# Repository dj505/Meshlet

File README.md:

# [Meshlet V2](https://5panel.dance/Meshlet)

Meshlet is an open-source and feature-packed LoRa mesh network node, designed to be compatible (but not affiliated) with the Meshtastic® project. It's made to be deployed just about anywhere you want it to be - you can plug in a solar panel and set it up outside, turn it into a pocketable every-day-carry node, wire it up to your car as a mobile repeater, or even just leave it on a windowsill attached to a BBS script/Meshsense/etc. 

**Table of Contents**
1. [Features](#features)
2. [Project Sponsor](#project-sponsor)
3. [Real World Testing](#real-world-testing)
5. [Meshlet Docs](#meshlet-docs)

## Features
Features include, but are not limited to...
- USB C, with configurable charge rate limit (250mA, 500mA, 1A)
- LiPo/LiIon and LiFePo4 support
- ESD/TVS protection on the USB port
- Solar input (as well as constant DC input) from 3.3V to 18V, tolerant up to 25V
  - Flexible wiring methods, with dedicated JST PH footprints as well as pads to directly solder wires to!
  - Tested & working with as little as a cheap 80mm 5v solar panel, on an overcast Canadian winter day!
  - Unlike many boards that need a manual reset after too little sunlight drains the battery, the Meshlet should recover on its own!
- Smart power path management, thanks to the BQ25185. No need to worry about unnecessarily cycling the battery!
- JST 2.0 and Picoblade 1.5mm battery connector footprints, to hopefully fit whatever LiPos you've got laying around
- Low operating power, measuring as low as 2.8mA idle current draw (without WiFi)
- Active current/voltage monitoring and reporting on 3 channels over the mesh, via INA3221
  - Ch. 1: Battery
  - Ch. 2: USB & external power
  - Ch. 3: BQ25185 regulated battery output
- Up to 8MB onboard flash
- WIO-SX1262 LoRa radio
- BME280 temperature/humidity/barometric pressure sensor
- I2C expansion port
- Dedicated 3.3V regulators for all major components, each with its own self-resetting fuse, to ensure stable power
- "External notification" header for a MOSFET-driven 3.3V buzzer, LED, vibration motor, etc
- Raspberry Pi RM2 for optional WiFi (and Bluetooth, whenever the firmware supports it)
- Total footprint size of ~42*32mm, less than half the size of a credit card!

## Project Sponsor
This project is sponsored by [PCBWay](https://pcbway.com)! Absolutely massive thank you to them for helping make these projects possible for me.

If you're interested in DIY electronics, I'm sure you're familiar with the name. PCBWay is a manufacturing company specializing in circuit boards, but they also offer services for SMT assembly, CNC milling, 3D printing, sheet metal fabrication, and injection molding! They can manufacture all of the parts for your hobby project, in one convenient place, with fine-grained control over the entire manufacturing process.

I relied pretty heavily on their PCB manufacturing and SMT assembly services to get the final revision of the Meshlet project built & tested. In my past experience, their boards always come out beautiful and pretty near perfect, and these ones are no exception. Their engineers were in contact with me from start to finish, making sure that everything was correct and to spec throughout each step of the process. They sourced all of the parts based on the BOM I provided, ensured that each pick lined up with what I needed, and even sent confirmation photos before the assembly process to ensure that every part was placed & oriented properly. When I mistakenly selected two parts to fit a single footprint, they agreed with my request to ship me the extra parts that I had them order alongside the PCBs, for me to solder by hand if needed after I receive them!

Sponsors like this make a huge difference in allowing me to continue testing & iterating on projects like this one. Without this opportunity, it likely would have stopped at the first revision prototype! Thanks again to PCBWay for reaching out and organizing this opportunity. Please [check them out](https://pcbway.com), and definitely consider using their services for your next project! 

## Real World Testing
Meshlet has been tested in a variety of real-world use cases thus far, including...
- **Building side solar repeater:** An early Meshlet V2 revision (1.0) installed inside a weatherproof box, with a 5V solar panel and 3000mAh LiPo, in late winter conditions. Runs Meshtastic in CLIENT_BASE mode. Uptime as of writing is roughly a month, with zero resets or brownouts. Battery life has not dropped below 40%. Average draw is 28-32mA, plus an extra 8-12mA due to a secondary nRF52 MeshCore repeater node being powered via the 3v3 peripheral pins.
- **Cheap garden light repeater:** A latest revision Meshlet V2 (1.1) installed inside a cheap solar garden light from Home Depot. Solar panel has been wired directly to the solar input. Powered by two 1000mAh parallel LiFePO4 18500 batteries that came with the light. Has not yet dropped below 50% in 1 week of testing. Runs MeshCore, as a repeater.
- **Handheld unit:** An early revision Meshlet V2 (1.0) in a custom 3D printed case, with an I2C OLED and M5Stack CardKB soldered to the I2C breakout. Powered by a 3000mAh battery. Running Meshtastic. Has not yet undergone extensive testing, but showed promise with a battery life lasting at least 3 days with the CLIENT_MUTE role.
- **Bench testing:** Early revision Meshlet V2 (1.0) in the plastic case from a Heltec T114, powered by a recycled 1000mAh vape battery. Has undergone testing with several different solar panels (4V-7V), DC power supplies (5V-12V), charge rates, and I2C peripherals. Has been able to handle everything I've thrown at it so far. Survived having both a solar panel and a battery being plugged in with the incorrect polarity on separate occasions.

## Meshlet Docs
Assembly notes, firmware, and usage notes can all be found on [the Meshlet webpage.](https://www.5panel.dance/Meshlet/)

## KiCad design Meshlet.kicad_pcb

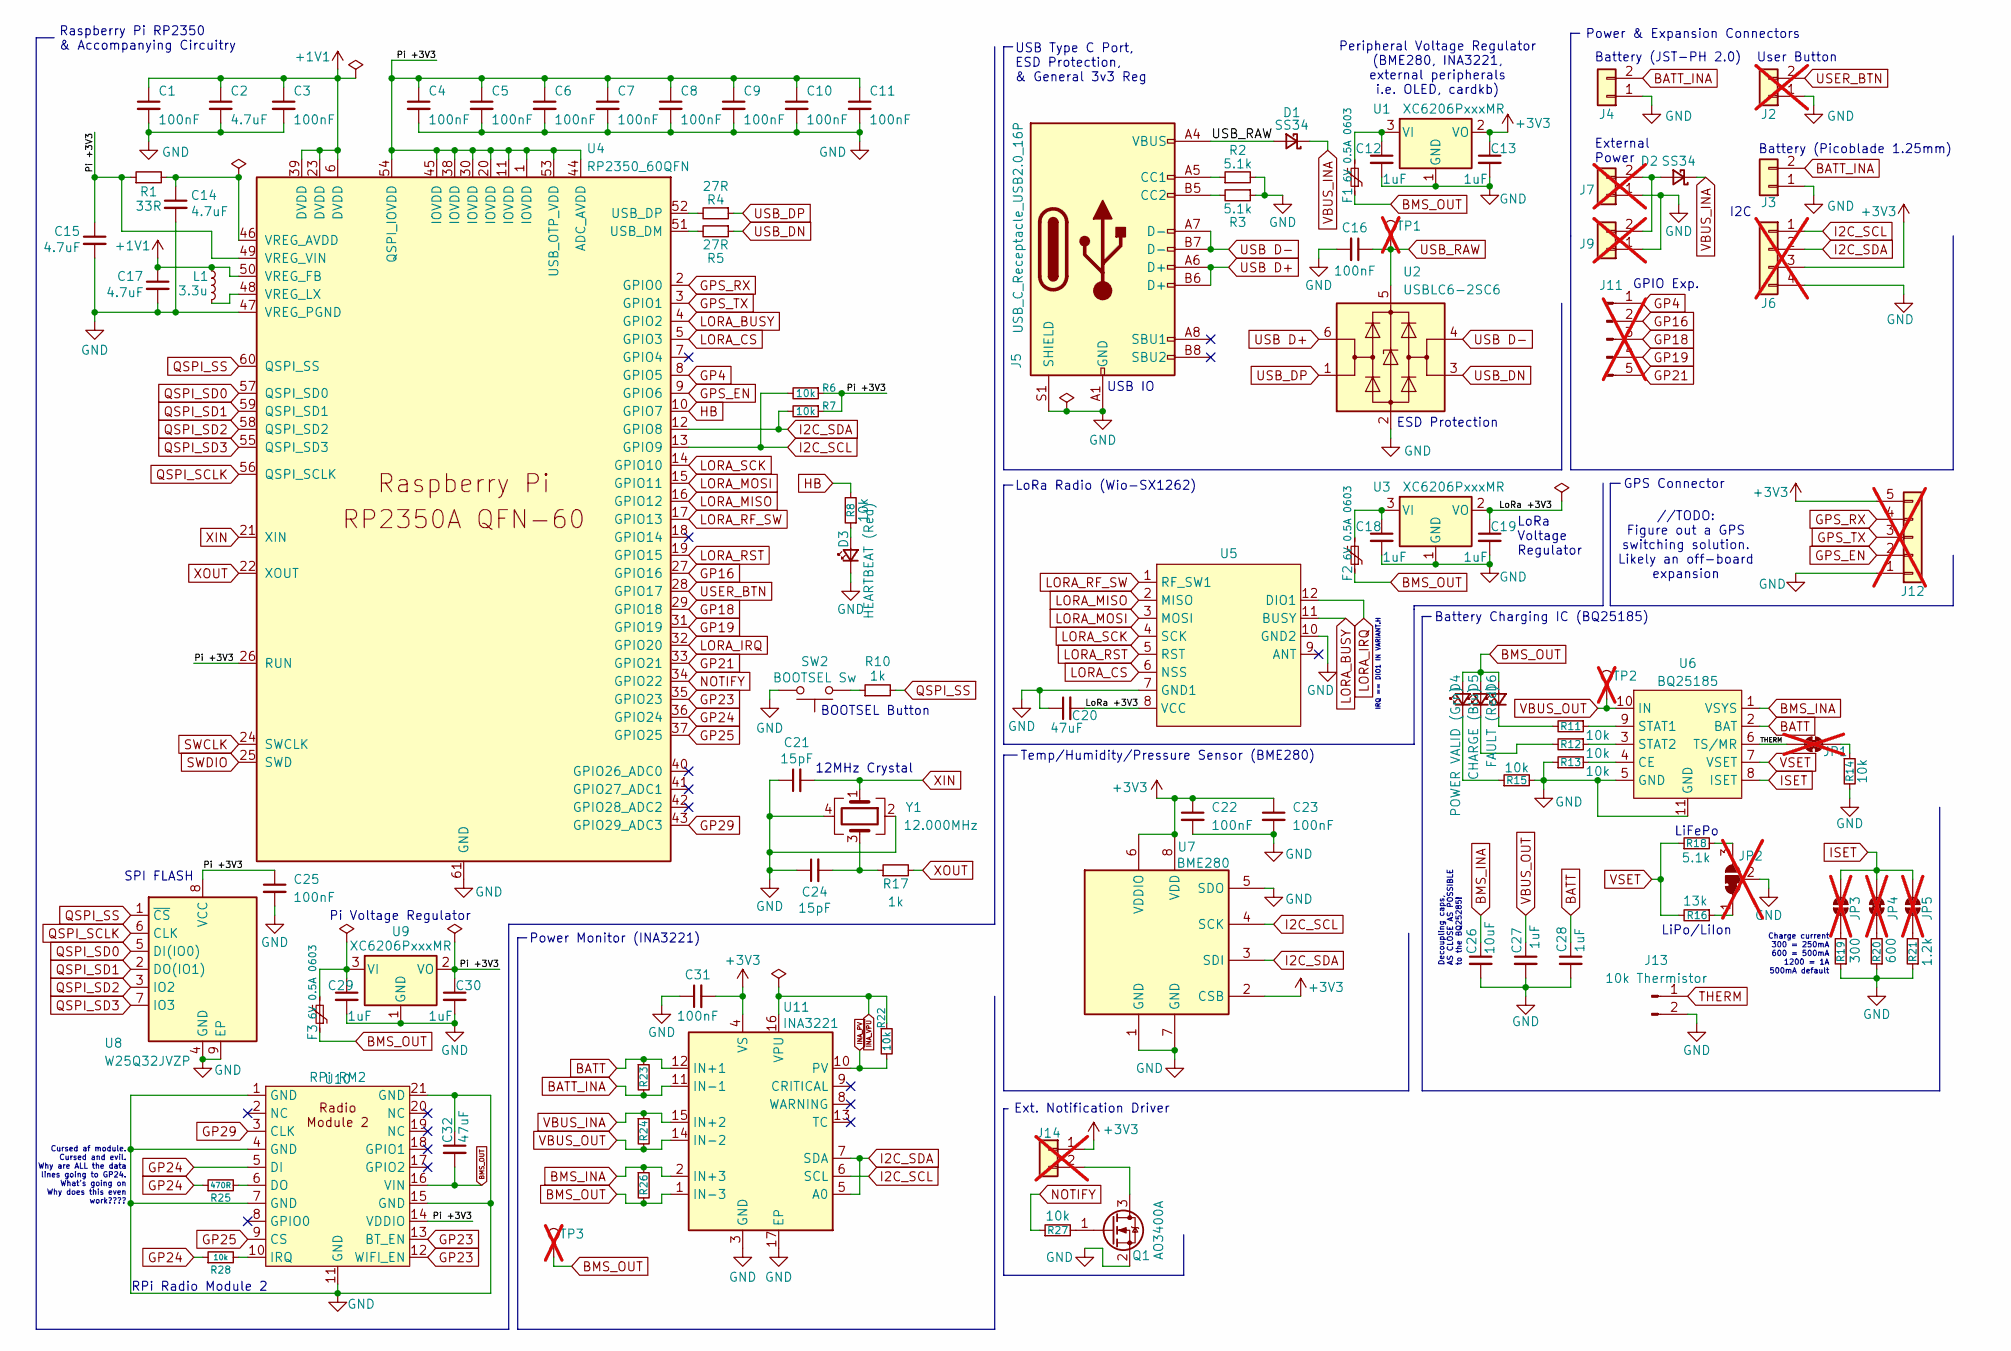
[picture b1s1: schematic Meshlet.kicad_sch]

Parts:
C1, C3, C4, C5, C6, C7, C8, C9, C10, C11, C16, C22, C23, C25, C31: 100nF; C_0402_1005Metric; LCSC C1525
C2, C14: 4.7uF; C_0402_1005Metric; LCSC C23733
C12, C13, C18, C19, C29, C30: 1uF; C_0402_1005Metric; LCSC C52923
C15, C17: 4.7uF; C_0402_1005Metric_small_pads; LCSC C23733
C20, C32: 47uF; C_0805_2012Metric; LCSC C16780
C21, C24: 15pF; C_0402_1005Metric; LCSC C1548
C26: 10uF; C_0402_1005Metric; LCSC C105226
C27, C28: 1uF; C_0402_1005Metric; LCSC C105226
D1, D2: SS34; D_SMA; LCSC C8678
D3: HEARTBEAT (Red); LED_0603_1608Metric; LCSC C2290
D4: POWER VALID (Grn); LED_0603_1608Metric; LCSC C2290
D5: CHARGE (Blu); LED_0603_1608Metric; LCSC C2290
D6: FAULT (Red); LED_0603_1608Metric; LCSC C2286
F1, F2, F3: 6V 0.5A 0603; Fuse_0603_1608Metric; LCSC C69679
J2: User Btn Header; PinHeader_1x02_P2.00mm_Vertical; not fitted
J3: Batt. Header (Picoblade 1.25); Molex_PicoBlade_53261-0271_1x02-1MP_P1.25mm_Horizontal; LCSC C177225
J4: Batt. Header (JST-PH 2.0); JST_PH_S2B-PH-SM4-TB_1x02-1MP_P2.00mm_Horizontal; LCSC C47647
J5: USB_C_Receptacle_USB2.0_16P; USB_C_Receptacle_G-Switch_GT-USB-7010ASV; LCSC C393939
J6: I2C Header; PinHeader_1x04_P2.00mm_Vertical; not fitted
J7: Ext. Power Header; JST_PH_S2B-PH-SM4-TB_1x02-1MP_P2.00mm_Horizontal; LCSC C27910; not fitted
J9: Ext. Power Header; PinHeader_1x02_P2.54mm_Vertical; not fitted
J11: GPIO Exp.; PinHeader_1x05_P2.00mm_Vertical; not fitted
J12: GPS Header; PinHeader_1x05_P1.27mm_Vertical; not fitted
J13: 10k Thermistor; PinHeader_1x02_P2.54mm_Vertical
J14: Ext. Notif. Header; PinHeader_1x02_P2.00mm_Vertical; not fitted
JP1: TS; SolderJumper-2_P1.3mm_Bridged_RoundedPad1.0x1.5mm; not fitted
JP2: Chemistry Select; SolderJumper-3_P1.3mm_Bridged12_RoundedPad1.0x1.5mm; not fitted
JP3: 250mA Charge; SolderJumper-2_P1.3mm_Open_RoundedPad1.0x1.5mm; not fitted
JP4: 500mA Charge; SolderJumper-2_P1.3mm_Bridged_RoundedPad1.0x1.5mm; not fitted
JP5: 1A Charge; SolderJumper-2_P1.3mm_Open_RoundedPad1.0x1.5mm; not fitted
L1: 3.3u; L_pol_2016; LCSC C42411119
Q1: AO3400A; SOT-23; LCSC C20917
R1: 33R; R_0402_1005Metric; LCSC C25105
R2, R3, R18: 5.1k; R_0402_1005Metric; LCSC C25905
R4, R5: 27R; R_0402_1005Metric; LCSC C25100
R6, R7, R8, R11, R12, R13, R14, R15, R22, R27, R28: 10k; R_0402_1005Metric; LCSC C25744
R10, R17: 1k; R_0402_1005Metric; LCSC C11702
R16: 13k; R_0402_1005Metric; LCSC C25754
R19: 300; R_0402_1005Metric; LCSC C25102
R20: 600; R_0402_1005Metric; LCSC C25126
R21: 1.2k; R_0402_1005Metric; LCSC C25862
R23, R24, R26: PA2512FKF7W0R01E; R_2512_6332Metric; LCSC C875838
R25: 470R; R_0402_1005Metric; LCSC C25117
SW2: BOOTSEL Sw; SW_Push_1P1T_XKB_TS-1187A; LCSC C318884
TP1, TP2, TP3: TestPoint; TestPoint_Pad_D1.0mm; not fitted
U1, U3, U9: XC6206PxxxMR; SOT-23-3; LCSC C5446
U2: USBLC6-2SC6; SOT-23-6; LCSC C2687116
U4: RP2350_60QFN; RP2350-QFN-60-1EP_7x7_P0.4mm_EP3.4x3.4mm_ThermalVias; LCSC C42411118
U5: Wio-SX1262
U6: BQ25185; Texas_DLH0010A_WSON-10-1EP_2.2x2mm_P0.4mm_EP0.9x1.5mm_Therm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; LCSC C19725033
U7: BME280; Bosch_LGA-8_2.5x2.5mm_P0.65mm_ClockwisePinNumbering; LCSC C92489
U8: W25Q32JVZP; WSON-8-1EP_6x5mm_P1.27mm_EP3.4x4.3mm; LCSC C2940197
U10: RPi RM2; Radio Module 2
U11: INA3221; Texas_RGV0016A_VQFN-16-1EP_4x4mm_P0.65mm_EP2.1x2.1mm; LCSC C181255
Y1: 12.000MHz; Crystal_SMD_3225-4Pin_3.2x2.5mm; LCSC C20625731

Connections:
+1V1: C1.1, C2.1, C3.1, C17.1, L1.1, U4.6 (DVDD), U4.23 (DVDD), U4.39 (DVDD), U4.50 (VREG_FB)
+3V3: C13.1, C22.1, C23.1, C31.2, J6.3, J12.5, J14.1, U1.2 (VO), U7.2 (CSB), U7.6 (VDDIO), U7.8 (VDD), U11.4 (VS)
/LoRa +3V3: C19.1, C20.2, U3.2 (VO), U5.8 (VCC)
/Pi +3V3: C4.1, C5.1, C6.1, C7.1, C8.1, C9.1, C10.1, C11.1, C15.1, C25.1, C30.1, R1.1, R6.1, R7.1, U4.1 (IOVDD), U4.11 (IOVDD), U4.20 (IOVDD), U4.26 (RUN), U4.30 (IOVDD), U4.38 (IOVDD), U4.44 (ADC_AVDD), U4.45 (IOVDD), U4.49 (VREG_VIN), U4.53 (USB_OTP_VDD), U4.54 (QSPI_IOVDD), U8.8 (VCC), U9.2 (VO), U10.14 (VDDIO)
BATT: C28.1, R23.1, U6.2 (BAT), U11.12 (IN+1)
BATT_INA: J3.2, J4.2, R23.2, U11.11 (IN-1)
BMS_INA: C26.1, R26.1, U6.1 (VSYS), U11.2 (IN+3)
BMS_OUT: C32.2, D4.2 (A), D5.2 (A), D6.2 (A), F1.1, F2.1, F3.1, R26.2, TP3.1, U10.16 (VIN), U11.1 (IN-3)
GND: C1.2, C2.2, C3.2, C4.2, C5.2, C6.2, C7.2, C8.2, C9.2, C10.2, C11.2, C12.2, C13.2, C14.2, C15.2, C16.2, C17.2, C18.2, C19.2, C20.1, C21.1, C22.2, C23.2, C24.1, C25.2, C26.2, C27.2, C28.2, C29.2, C30.2, C31.1, C32.1, D3.1 (K), J2.1, J3.1, J4.1, J5.A1 (GND), J5.A12 (GND), J5.B1 (GND), J5.B12 (GND), J5.S1 (SHIELD), J6.4, J7.1, J9.1, J12.1, J13.2, JP2.2 (C), Q1.2 (S), R2.2, R3.1, R13.1, R14.2, R15.2, R19.1, R20.1, R21.1, SW2.2, U1.1 (GND), U2.2 (GND), U3.1 (GND), U4.47 (VREG_PGND), U4.61 (GND), U5.7 (GND1), U5.10 (GND2), U6.5 (GND), U6.11 (GND), U7.1 (GND), U7.5 (SDO), U7.7 (GND), U8.4 (GND), U8.9 (EP), U9.1 (GND), U10.1 (GND), U10.4 (GND), U10.7 (GND), U10.11 (GND), U10.15 (GND), U10.21 (GND), U11.3 (GND), U11.17 (EP), Y1.2, Y1.4
GP4: J11.1, U4.8 (GPIO5)
GP16: J11.2, U4.27 (GPIO16)
GP18: J11.3, U4.29 (GPIO18)
GP19: J11.4, U4.31 (GPIO19)
GP21: J11.5, U4.33 (GPIO21)
GP23: U4.35 (GPIO23), U10.12 (WIFI_EN), U10.13 (BT_EN)
GP24: R25.1, R28.1, U4.36 (GPIO24), U10.5 (DI)
GP25: U4.37 (GPIO25), U10.9 (CS)
GP29: U4.43 (GPIO29_ADC3), U10.3 (CLK)
GPS_EN: J12.2, U4.9 (GPIO6)
GPS_RX: J12.4, U4.2 (GPIO0)
GPS_TX: J12.3, U4.3 (GPIO1)
HB: R8.2, U4.10 (GPIO7)
I2C_SCL: J6.1, R6.2, U4.13 (GPIO9), U7.4 (SCK), U11.6 (SCL)
I2C_SDA: J6.2, R7.2, U4.12 (GPIO8), U7.3 (SDI), U11.5 (A0), U11.7 (SDA)
INA_PV: R22.2, U11.10 (PV)
INA_VPU: R22.1, U11.16 (VPU)
ISET: JP3.2 (B), JP4.2 (B), JP5.2 (B), U6.8 (ISET)
LORA_BUSY: U4.4 (GPIO2), U5.11 (BUSY)
LORA_CS: U4.5 (GPIO3), U5.6 (NSS)
LORA_IRQ: U4.32 (GPIO20), U5.12 (DIO1)
LORA_MISO: U4.16 (GPIO12), U5.2 (MISO)
LORA_MOSI: U4.15 (GPIO11), U5.3 (MOSI)
LORA_RF_SW: U4.17 (GPIO13), U5.1 (RF_SW1)
LORA_RST: U4.19 (GPIO15), U5.5 (RST)
LORA_SCK: U4.14 (GPIO10), U5.4 (SCK)
NOTIFY: R27.1, U4.34 (GPIO22)
unnamed: C24.2, R17.1, Y1.3
unnamed: D2.2 (A), J7.2, J9.2
unnamed: D3.2 (A), R8.1
unnamed: D4.1 (K), R15.1
unnamed: D5.1 (K), R12.2
unnamed: D6.1 (K), R11.2
unnamed: J5.A5 (CC1), R2.1
unnamed: J5.B5 (CC2), R3.2
unnamed: J14.2, Q1.3 (D)
unnamed: JP1.2 (B), R14.1
unnamed: JP2.1 (A), R16.1
unnamed: JP2.3 (B), R18.2
unnamed: JP3.1 (A), R19.2
unnamed: JP4.1 (A), R20.2
unnamed: JP5.1 (A), R21.2
unnamed: Q1.1 (G), R27.2
unnamed: R10.1, SW2.1
unnamed: C12.1, F1.2, U1.3 (VI)
unnamed: C18.1, F2.2, U3.3 (VI)
unnamed: R5.2, U4.51 (USB_DM)
unnamed: R4.2, U4.52 (USB_DP)
unnamed: C14.1, R1.2, U4.46 (VREG_AVDD)
unnamed: L1.2, U4.48 (VREG_LX)
unnamed: R13.2, U6.4 (CE)
unnamed: R11.1, U6.9 (STAT1)
unnamed: R12.1, U6.3 (STAT2)
unnamed: C29.1, F3.2, U9.3 (VI)
unnamed: R25.2, U10.6 (DO)
unnamed: R28.2, U10.10 (IRQ)
QSPI_SCLK: U4.56 (QSPI_SCLK), U8.6 (CLK)
QSPI_SD0: U4.57 (QSPI_SD0), U8.5 (DI(IO0))
QSPI_SD1: U4.59 (QSPI_SD1), U8.2 (DO(IO1))
QSPI_SD2: U4.58 (QSPI_SD2), U8.3 (IO2)
QSPI_SD3: U4.55 (QSPI_SD3), U8.7 (IO3)
QSPI_SS: R10.2, U4.60 (QSPI_SS), U8.1 (~CS)
SWCLK: U4.24 (SWCLK)
SWDIO: U4.25 (SWD)
THERM: J13.1, JP1.1 (A), U6.6 (TS/MR)
USB D+: J5.A6 (D+), J5.B6 (D+), U2.6 (I/O1)
USB D-: J5.A7 (D-), J5.B7 (D-), U2.4 (I/O2)
USB_DN: R5.1, U2.3 (I/O2)
USB_DP: R4.1, U2.1 (I/O1)
USB_RAW: C16.1, D1.2 (A), J5.A4 (VBUS), J5.A9 (VBUS), J5.B4 (VBUS), J5.B9 (VBUS), TP1.1, U2.5 (VBUS)
USER_BTN: J2.2, U4.28 (GPIO17)
VBUS_INA: D1.1 (K), D2.1 (K), R24.1, U11.15 (IN+2)
VBUS_OUT: C27.1, R24.2, TP2.1, U6.10 (IN), U11.14 (IN-2)
VSET: R16.2, R18.1, U6.7 (VSET)
XIN: C21.2, U4.21 (XIN), Y1.1
XOUT: R17.2, U4.22 (XOUT)

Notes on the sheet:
Charge current 300 = 250mA 600 = 500mA 1200 = 1A 500mA default
I2C
LoRa Voltage Regulator
IRQ == DIO1 IN VARIANT.H
12MHz Crystal
LiFePo
Pi Voltage Regulator
SPI FLASH
Power Monitor (INA3221)
Cursed af module. Cursed and evil. Why are ALL the data lines going to GP24. What's going on Why does this even work????
Battery Charging IC (BQ25185)
Battery (JST-PH 2.0)
External Power
LoRa Radio (Wio-SX1262)
User Button
ESD Protection
Power & Expansion Connectors
Ext. Notification Driver
USB Type C Port, ESD Protection, & General 3v3 Reg
Raspberry Pi RP2350 & Accompanying Circuitry
Peripheral Voltage Regulator (BME280, INA3221, external peripherals i.e. OLED, cardkb)
//TODO: Figure out a GPS switching solution. Likely an off-board expansion
Temp/Humidity/Pressure Sensor (BME280)
GPIO Exp.
USB IO
Decoupling caps, AS CLOSE AS POSSIBLE to the BQ25285!
RPi Radio Module 2
LiPo/LiIon
Battery (Picoblade 1.25mm)
GPS Connector
BOOTSEL Button

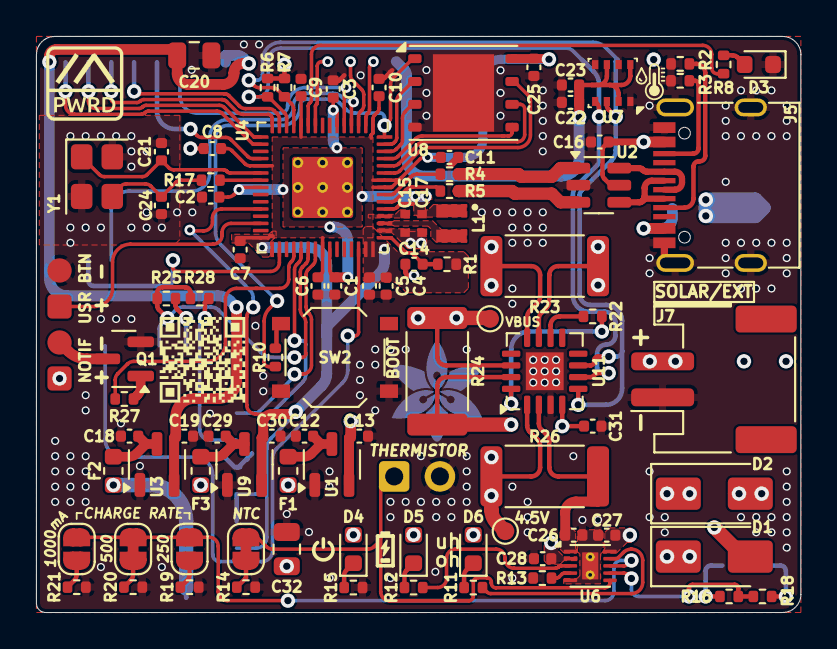
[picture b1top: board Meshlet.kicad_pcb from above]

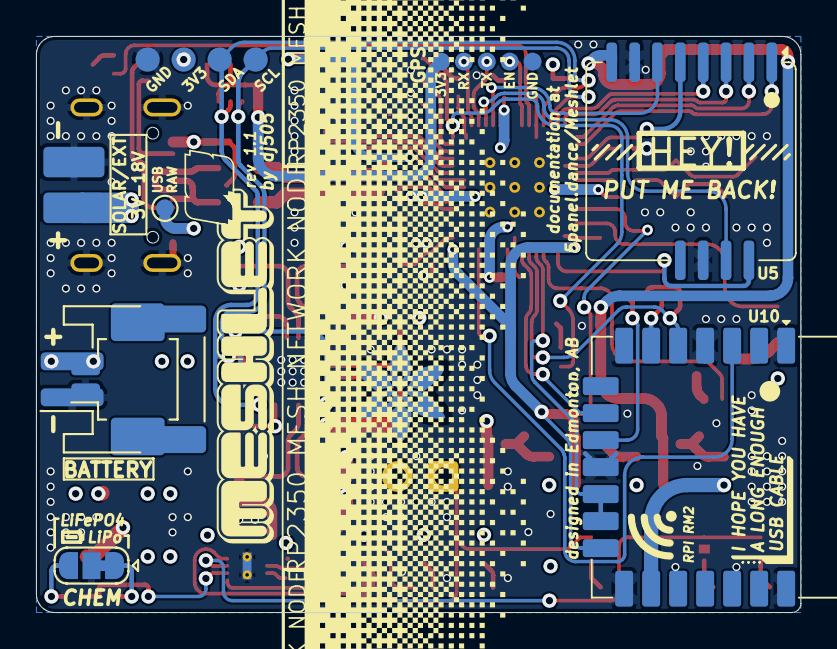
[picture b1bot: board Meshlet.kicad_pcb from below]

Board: 4 copper layers, 42.5 x 32.0 mm, 101 parts (9 on the bottom side), 78 nets.

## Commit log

2025-07-21 Initial commit - finished schematic
2025-07-27 PCB routing like 99% done oops
2025-08-03 Custom Pi RM2 symbol/footprint, silkscreen gfx
2025-08-03 Tooling holes, silkscreen changes
2025-08-03 fix picoblade battery polarity hopefully 🤞
2025-08-03 Fixed exposed ground between jumper pads, yikes
2025-08-04 appease the trademark gods
2025-08-05 docs
2025-08-05 haha oops
2025-08-06 Fixed stemma port pin order, more touchups
2025-08-06 Ground fill thermal spoke bug workaround for RM2
2025-08-07 Better thermal relief bug workaround?
2025-08-14 Silkscreen changes, added BQ24074 output breakout
2025-12-29 Fixed several design flaws. More caps, more LDOs, etc
2026-01-03 Major changes to schematic
    Replace BQ24074 with BQ25185, remove extraneous passives, simplified several areas, add extra GPIO breakouts, reannotated schematic, etc.
2026-01-07 Redesign!
2026-01-09 4 layer ver. complete!
2026-01-10 Graphics!
2026-01-11 Small changes
2026-01-11 silkscreen tweaks
2026-01-12 Silkscreen tweaks, update docs
2026-01-13 Add interactive BOM
2026-01-13 Updated docs
2026-01-13 Add GPS header
2026-01-13 GPS header labels
2026-01-13 Add test points for power
2026-01-13 Trace tuning, silkscreen touch-ups, BOM touch-ups
2026-01-13 I knew something was missing. Lil thermometer icon
2026-01-14 Trace and zone tune-ups
2026-01-14 Rounded all of the traces on the top layer. For fun
2026-01-15 Rounded traces on the back side too, updated ibom
2026-01-16 Just in case commit before changing via stitching
2026-01-16 Bigger vias. Less manufacturing fees. I hope
2026-01-16 accidentally shorted the inner layers oops
2026-02-23 Fix text sizes for production, fix batt chem label
2026-02-23 R16/R18 silkscreen labels swapped, fixed
2026-02-23 Hopefully last little silkscreen fix
2026-02-23 ibom updates
2026-02-23 Replaced C26-28 22uF with basic 1uF/10uF caps
2026-02-23 Clean up BOM & iBOM
2026-02-23 Silkscreen cleanup
2026-02-23 Regenerate iBOM
2026-02-23 Update docs
2026-04-18 Update index.html
    Add sponsor segment
